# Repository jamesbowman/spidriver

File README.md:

Full documentation is at
[spidriver.com](https://spidriver.com).

SPIDriver is a tool for controlling any SPI device from your PC's USB port.
It connects as a standard USB serial device, so there are no drivers to install.
The serial protocol is [very simple](/protocol.md),
and there are included drivers for

* Windows/Mac/Linux GUI
* Windows/Mac/Linux command-line
* Python 2 and 3
* Windows/Mac/Linux C/C++

## Contributed language bindings

The following bindings were contributed by SPIDriver community members:

* **.net** https://github.com/alandoherty/spidriver-net
* **rust** https://docs.rs/spidriver/0.1.0/spidriver/

[spidriver.com](https://spidriver.com)

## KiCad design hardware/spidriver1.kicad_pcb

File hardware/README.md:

This is the PCB for the SPIDriver.
It uses a [SKiDL](https://github.com/xesscorp/skidl) to define the netlist.

PCB layout is done in KiCAD's pcbnew:

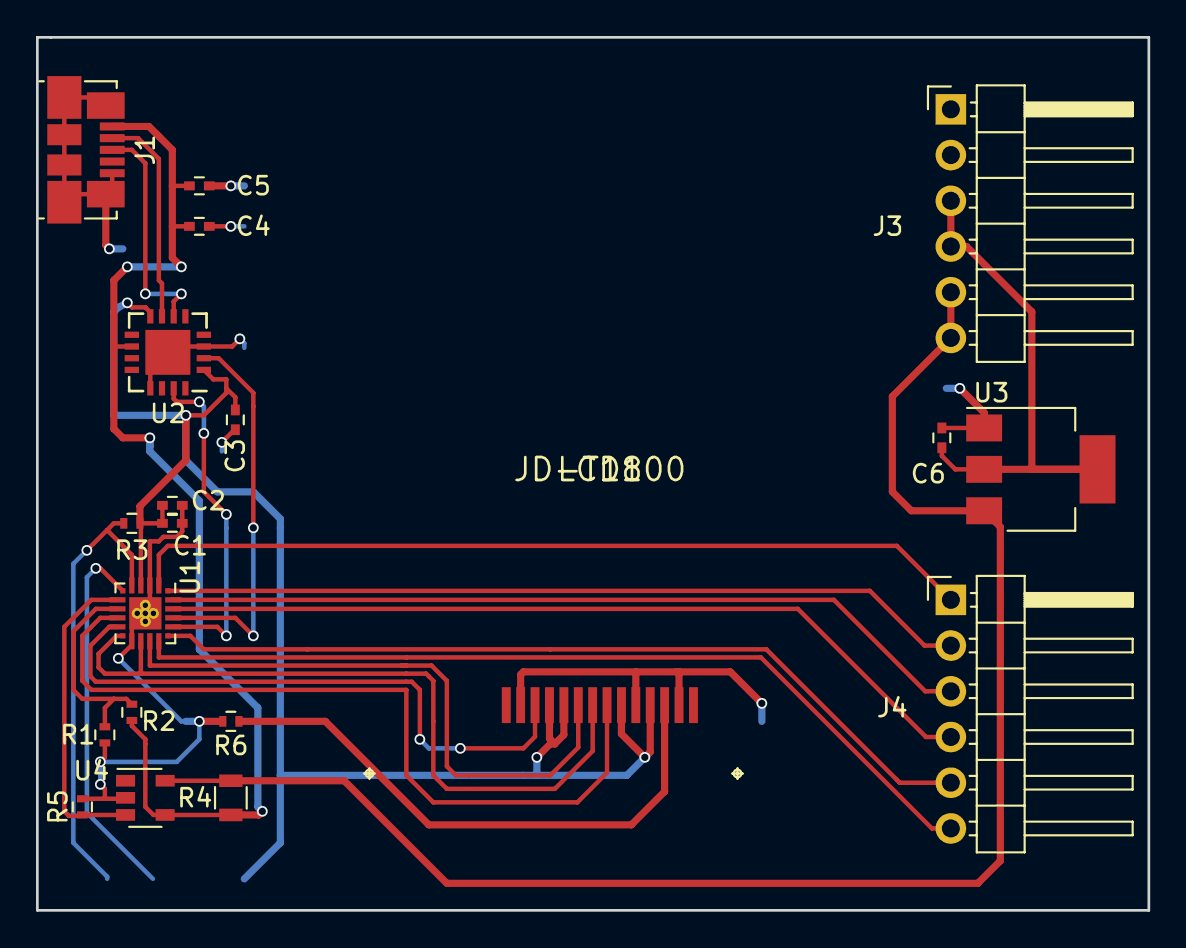
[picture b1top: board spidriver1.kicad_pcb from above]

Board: 2 copper layers, 61.8 x 48.5 mm, 21 parts (1 on the bottom side), 24 nets.

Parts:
C1, C3, C4, C6: 0.1uF; C_0402
C2: 1uF; C_0402
C5: 10uF; C_0402
J1: USB_OTG; USB_Micro-B_Molex_47346-0001
J2: Conn_01x04_Male; POGO4
J3, J4: Conn_01x06_Male; Pin_Header_Angled_1x06_Pitch2.54mm
LCD1: JD-T1800
R1: 1180; R_0402
R2: 1000; R_0402
R3: 1K; R_0402
R4: .1; R_0805
R5: 12K; R_0402
R6: 22; R_0402
U1: EFM8BB10F8G-A-QFN20; SiliconLabs_QFN-20-1EP_3x3mm_Pitch0.5mm_ThermalVias
U2: FT230XQ; QFN-16-1EP_4x4mm_Pitch0.65mm
U3: AP1117-15; SOT-223-3Lead_TabPin2
U4: ZXCT1110; SOT-23-5

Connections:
3.3V: C1.1, C2.1, C3.1, J2.1, LCD1.4, LCD1.6, LCD1.10, LCD1.11, R3.2, U1.4, U2.1, U2.8
3.3VB: C6.1, J3.3, J3.4, U3.2
5V: C4.1, C5.1, J1.1, R1.1, R4.1, U2.10, U4.4
5VB: J3.5, J3.6, R4.2, U3.3, U4.5
GND: C1.2, C2.2, C3.2, C4.2, C5.2, C6.2, J1.5, J1.6, J2.2, J3.1, J3.2, LCD1.2, LCD1.5, LCD1.13, R2.2, R5.2, R6.2, U1.3, U1.12, U1.21, U2.3, U2.13, U2.17, U3.1, U4.2
unnamed: R1.2, R2.1, U1.8
unnamed: J2.4, R3.1, U1.5
unnamed: U1.18, U2.2
unnamed: U1.17, U2.15
unnamed: R5.1, U1.7, U4.3
unnamed: J2.3, U1.6
unnamed: J4.1, U1.2
unnamed: J4.2, U1.1
unnamed: J4.3, U1.20
unnamed: J4.4, U1.19
unnamed: J4.5, U1.16
unnamed: J4.6, U1.15
unnamed: LCD1.9, U1.14
unnamed: LCD1.8, U1.11, U1.13
unnamed: LCD1.12, U1.10
unnamed: LCD1.7, U1.9
unnamed: LCD1.3, R6.1
unnamed: J1.3, U2.6
unnamed: J1.2, U2.7

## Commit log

2018-04-03 First images
2018-04-03 Describe features
2018-04-03 Close-up image
2018-04-03 Link to PCB image
2018-04-03 Feature list
2018-04-03 Add logo
2018-04-03 Fix typos
2018-05-03 C/C++ bindings for Linux
2018-05-03 Example of command-line usage
2018-05-03 Missing stdlib.h
2018-05-03 Using cfmakeraw() avoids hang on first read on rPi
2018-05-04 Python library import
2018-05-04 Version string in one place
2018-05-04 Enable Travis
2018-05-04 Travis fix
2018-05-04 Remve support for Python 2.6
2018-05-04 Add C utilities to Travis test
2018-05-05 LED string driver
2018-05-05 Slow down LED cycling
2018-05-05 Add writeread method
2018-05-05 Atmega ISP example
2018-05-06 Add CCITT CRC to C implementation
2018-05-07 Start of Gtk GUI
2018-05-07 Text entry
2018-05-08 loadimage demo
2018-05-09 CRC updates on both write and writeread
2018-05-09 Rename CRC field to ccitt_crc
2018-05-09 Report on clock drift
2018-05-12 Thrash sample
2018-05-14 Add support for "detach" command
2018-05-14 Full Atmega programmer
2018-05-22 Minor cleanups for Python2/3
2018-05-22 Format for 480x272
2018-05-22 Accept device name as first arg
2018-05-22 Accept device on command line
2018-06-04 Protocol writeup
2018-06-04 Document x command
2018-06-15 Add example of building and running command-line tool
2018-06-22 Import the win32 GUI
2018-06-22 Static link libstdc++, switch to true spidriver
2018-06-22 Win32 command-line takes device name
2018-06-22 Remove accidentally added file
2018-06-22 Silence more type warnings
2018-06-22 Rename Mac/Linux executable to spicl
2018-06-22 Fix missing/bad device flow
2018-06-22 Add firmware and hardware directories
2018-06-22 Clean up comments
2018-06-22 Fix phrasing
2018-06-22 import PCBnew
2018-06-25 Win32 GUI version looking OK
2018-07-06 Initial import, LCD panel sample
2018-07-06 Checkpoint, refactoring
2018-07-06 Refactored
2018-07-10 Properly resize and crop images for display
2018-07-10 Grace Hopper test image
2018-07-11 Sort imports. Remove unused
2018-07-11 Add encoding declarations
2018-07-11 PEP8 docstrings & remove redundant parens
2018-07-11 PEP8 whitespace
2018-07-11 Fix some print statements
2018-07-31 Add 256x256 icon. Use as Windows icon
2018-07-31 Remove Python 3.2 - no longer supported?
2018-07-31 Proper Windows installer using NSIS
2018-08-01 Place holder for wx GUI
2018-08-01 Clean up GTK gui
2018-08-02 Signals hooked up
2018-08-02 All widgets functional
2018-08-03 Device selection
2018-08-03 Clean up for Python3 and MacOS
2018-08-03 Proper name
2018-08-03 Cope with missing directory properly
2018-08-03 UI cleanups
    Enter key does transfer
    Device picker combobox is read-only
    Use monospace for logginmg window
2018-08-25 Update for actual module used
2018-08-25 Assert RESET properly
2018-08-26 Fix for Python 2
2018-08-26 Print bytes as unsigned
2018-08-26 Flash sample initial version
2018-08-26 Clean up for Python 3
2018-08-27 Rebuild everything script
2018-08-30 Implement behavior described in #7
2018-08-30 In the win32 common code, if portname starts with 'C' insert the prefix \\.\
    [#6]
2018-09-01 First cut of the iceprog
2018-09-01 Removed extraneous material
2018-09-02 Update with notes for Windows users
2018-09-02 minor edit
2018-09-02 Clean up
2018-09-02 Point everyone to official page
2018-09-04 Enable testing on both Linux and OSX
2018-09-04 Attempt reduced matrix
2018-09-04 testall exit on failed command
2018-09-04 fix baud rate on osx?
2018-09-04 move pyserial around
2018-09-04 Travis: try doing install --user
2018-09-04 Travis osx: testall is a shell script
2018-09-04 Travis osx: don't do --user install
2018-09-04 osx: include ioctl.h
2018-09-05 osx: properly set 460800 baud
2018-09-05 Pure Python RGB565 encoder for better portability
2018-09-07 Proper flash example, confirmed with ESP8266
2019-01-13 python/samples/flash.py: Add size option
    Some flash chips do not provide the flash size in the second byte of the
    device ID, which can either cause the wrong number of bytes to be
    read/written or cause idcode() to be called infinitely. The user must
    check their chip's datasheet to know whether its device ID includes its
    size or they need to specify the size with the -s option.
    Read tested with an Atmel AT26DF321 (manufacturer ID 0x1F, device ID
2019-01-13 .gitignore: Exclude built objects and executables
2019-04-28 Update home URL
2019-04-28 Clean compile on win32
2019-05-11 Modifications for MSVC
2019-07-01 Recognize size fields of 1-7 as valid. For FeRAM
    [#19]
2019-07-23 Multi flash/FRAM test board
2019-07-26 Work with new API
2020-01-24 Add links to .net and rust drivers
2021-02-10 Docs first attempt
2021-02-11 Generate all formats
2021-02-11 Version bump to 1.0.0
2021-02-12 Readthedocs badge
2021-03-31 Updates for spidriver2
2021-03-31 Version 1.1.0
2021-03-31 Mode support for spidriver2
2021-09-04 Document setmode
2021-09-04 version bump for documentation of setmode
2022-01-07 gui.py: Fixup to avoid deprecated warnings
2022-01-07 gui.py: Fix Button code to work correctly
    * Dont use deprecated function.
2022-02-25 spicl: improve command arg checking
    For 'w' and 'r', a missing argument would cause a segfault. For 'a',
    'b' and 'm', the command would just be ignored. Lets try to improve that
    a little.
2022-02-25 spicl: repeat sequence
    Really nice for clearing a display that needs an enable/disable around
    each byte.
2022-03-05 Fix warnings when building with warnings enabled
2022-05-06 Update st7735s.py
    Replace the `array.array('B', d565h.tostring())` with `array.array('B', d565h.tobytes())` to match deprecation in Python3.
2022-08-16 port to python3
2023-02-07 Fix link
